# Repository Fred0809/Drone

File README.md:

# Drone

This is a one shared repository for four separate ones I've been working on previously. It consists of Electronic Soeed Controller (ESC), Flight Controller Unit (FCU), Power Distribution Board (PDB), and Remote Controller (RC) hardware projects. The initial idea was supposed to use these four to make a working flying drone. Currently they only show what I've been doing when I first started PCB journey with some of design choices and my very limited knowledge and skillset back then. And at this time none of them is being worked on anymore.

ESC:

FCU:

PDB:

RC:

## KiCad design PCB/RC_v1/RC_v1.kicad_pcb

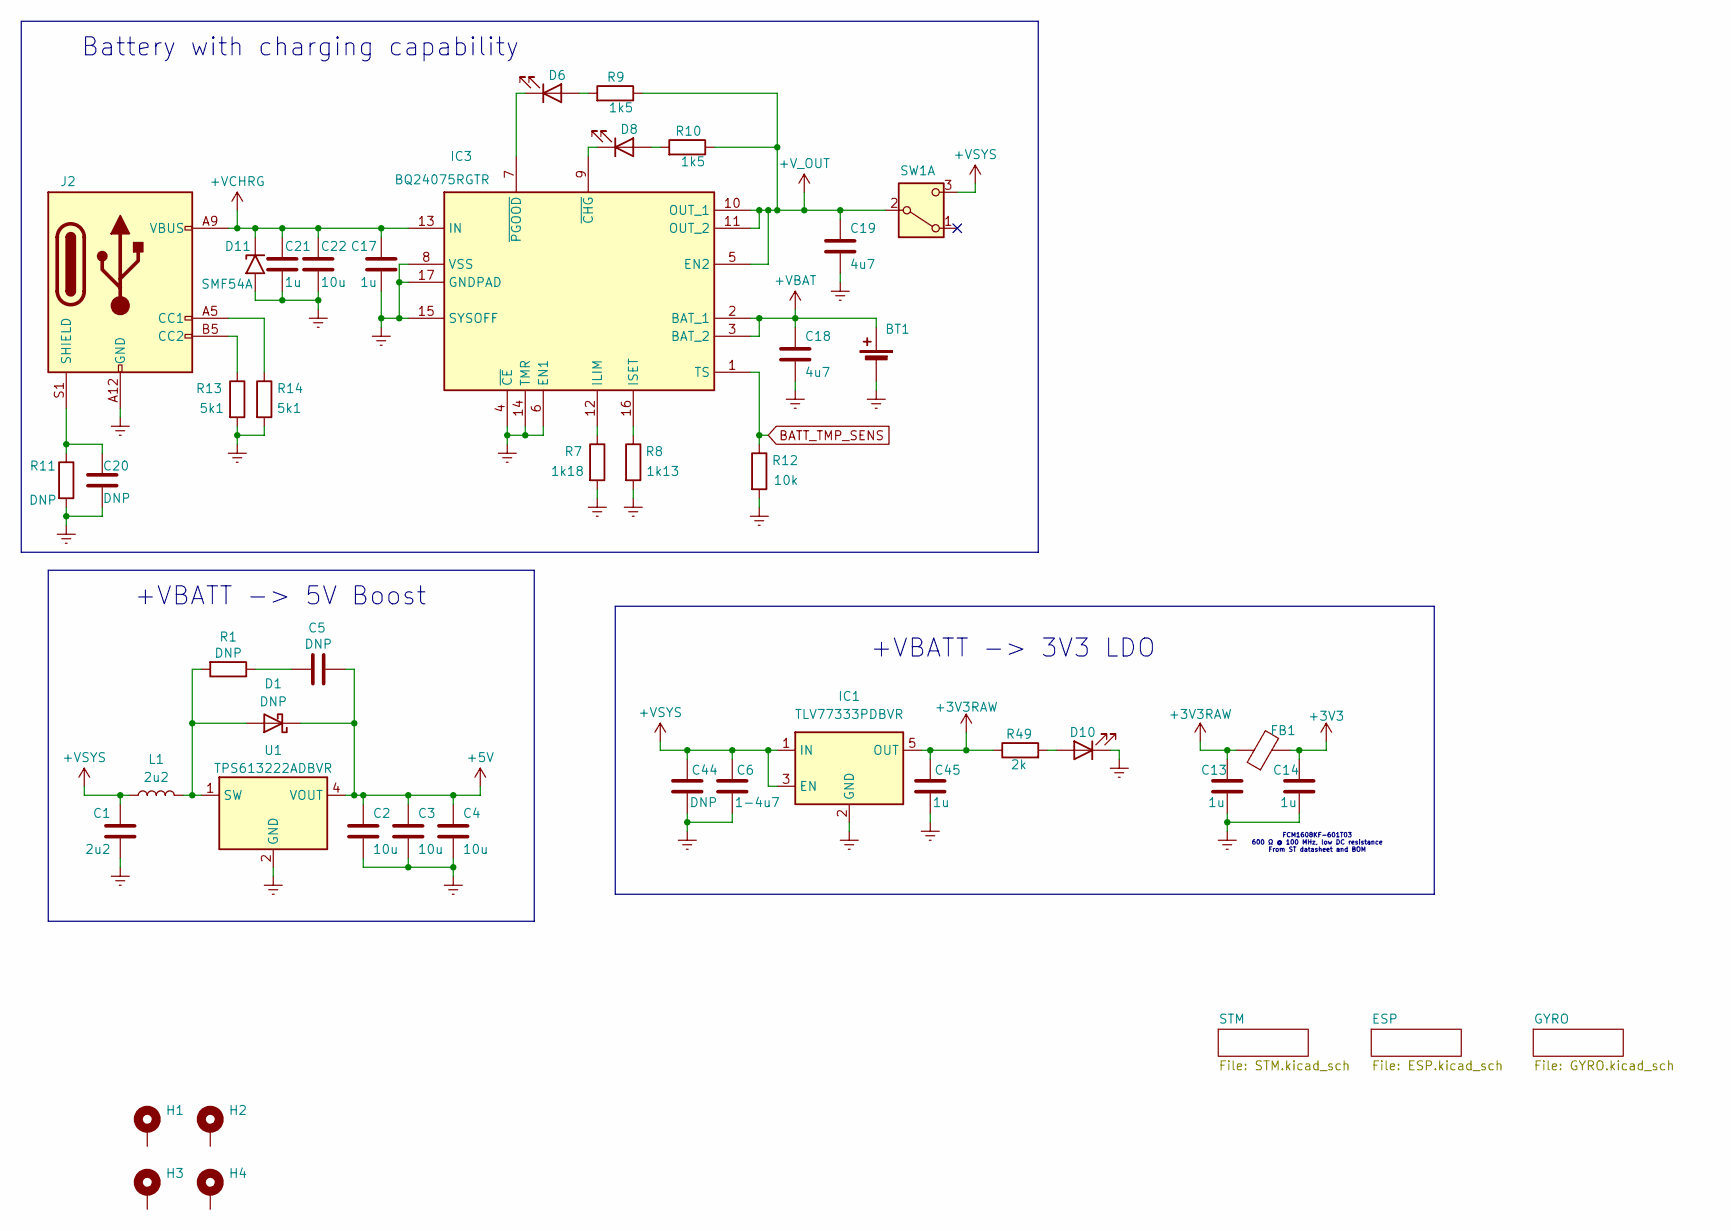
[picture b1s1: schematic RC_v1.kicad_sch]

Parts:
BT1: Battery_Cell
C1: 2u2; C_0603_1608Metric
C2, C3, C4, C22: 10u; C_0603_1608Metric
C5: DNP; C_0805_2012Metric
C6: 1-4u7; C_0603_1608Metric
C13, C14, C45: 1u; C_0603_1608Metric
C17, C21: 1u; C_0402_1005Metric
C18, C19: 4u7; C_0603_1608Metric
C20, C44: DNP; C_0603_1608Metric
D1: DNP; D_0603_1608Metric
D6, D8, D10: LED; LED_0805_2012Metric
D11: SMF54A; D_SMF
FB1: FCM1608KF-601T03; L_0603_1608Metric
H1, H2, H3, H4: MountingHole_Pad; MountingHole_2.2mm_M2_Pad
IC1: TLV77333PDBVR; SOT95P280X145-5N; Mouser Part Number 595-TLV77333PDBVR
IC3: BQ24075RGTR; QFN50P300X300X100-17N-D; Mouser Part Number 595-BQ24075RGTR
J2: USB_C_Receptacle_PowerOnly_6P; USB_C_Receptacle_GCT_USB4125-xx-x_6P_TopMnt_Horizontal
L1: 2u2; WE-MAPI_4020; Mouser Part Number 710-74438356022
R1, R11: DNP; R_0603_1608Metric
R7: 1k18; R_0603_1608Metric
R8: 1k13; R_0603_1608Metric
R9, R10: 1k5; R_0603_1608Metric
R12: 10k; R_0603_1608Metric
R13, R14: 5k1; R_0603_1608Metric
R49: 2k; R_0603_1608Metric
SW1: SW_DPDT_x2; SW_CK_JS202011AQN_DPDT_Angled
U1: TPS613222ADBVR; SOT-23-5

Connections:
+3V3: C14.1, FB1.2; also elsewhere on the board
+3V3RAW: C13.1, C45.1, FB1.1, IC1.5 (OUT), R49.1
+5V: C2.1, C3.1, C4.1, C5.2, D1.1 (K), U1.4 (VOUT); also elsewhere on the board
+VBAT: BT1.1 (+), C18.1, IC3.2 (BAT_1), IC3.3 (BAT_2)
+VCHRG: C17.1, C21.1, C22.1, D11.1 (A1), IC3.13 (IN), J2.A9 (VBUS), J2.B9 (VBUS)
+VSYS: C1.1, C6.1, C44.1, IC1.1 (IN), IC1.3 (EN), L1.1, SW1.3 (C)
+V_OUT: C19.1, IC3.5 (EN2), IC3.10 (OUT_1), IC3.11 (OUT_2), R9.1, R10.1, SW1.2 (B)
BATT_TMP_SENS: IC3.1 (TS), R12.1
GND: BT1.2 (-), C1.2, C2.2, C3.2, C4.2, C6.2, C13.2, C14.2, C17.2, C18.2, C19.2, C20.2, C21.2, C22.2, C44.2, C45.2, D10.1 (K), D11.2 (A2), IC1.2 (GND), IC3.4 (~CE), IC3.6 (EN1), IC3.8 (VSS), IC3.14 (TMR), IC3.15 (SYSOFF), IC3.17 (GNDPAD), J2.A12 (GND), J2.B12 (GND), R7.2, R8.2, R11.2, R12.2, R13.2, R14.2, U1.2 (GND); also elsewhere on the board
unnamed: C5.1, R1.1
unnamed: D1.2 (A), L1.2, R1.2, U1.1 (SW)
unnamed: D6.2 (A), R9.2
unnamed: D6.1 (K), IC3.7 (~PGOOD)
unnamed: D8.2 (A), R10.2
unnamed: D8.1 (K), IC3.9 (~CHG)
unnamed: D10.2 (A), R49.2
unnamed: IC3.12 (ILIM), R7.1
unnamed: IC3.16 (ISET), R8.1
unnamed: J2.A5 (CC1), R14.1
unnamed: J2.B5 (CC2), R13.1
unnamed: C20.1, J2.S1 (SHIELD), R11.1

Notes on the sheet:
FCM1608KF-601T03 600 Ω @ 100 MHz, low DC resistance From ST datasheet and BOM
+VBATT -> 3V3 LDO
Battery with charging capability
+VBATT -> 5V Boost

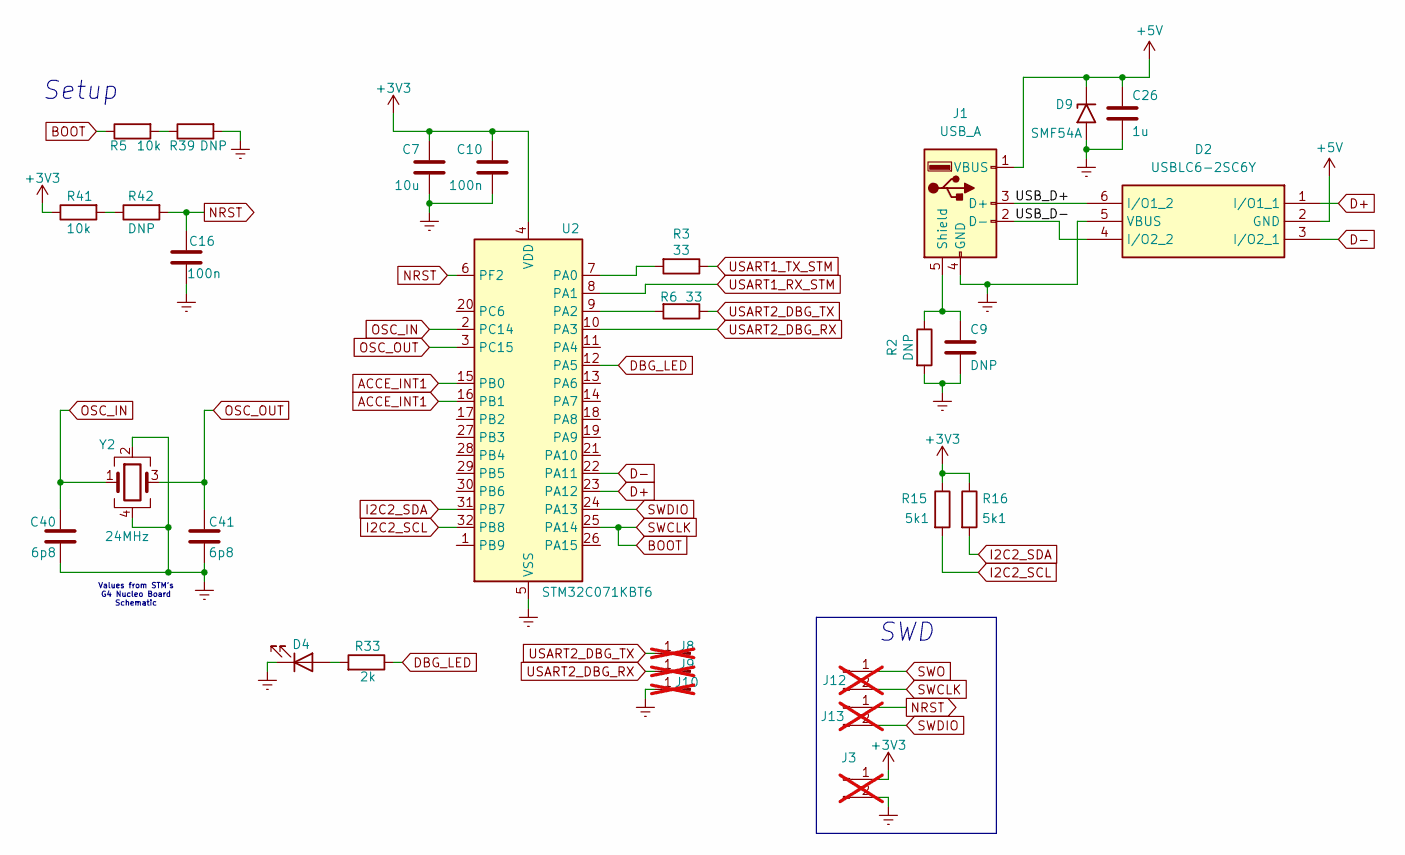
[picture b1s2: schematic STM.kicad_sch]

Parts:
C7: 10u; C_0603_1608Metric
C9: DNP; C_0603_1608Metric
C10, C16: 100n; C_0402_1005Metric
C26: 1u; C_0603_1608Metric
C40, C41: 6p8; C_0402_1005Metric
D2: USBLC6-2SC6Y; SOT95P280X145-6N; Mouser Part Number 511-USBLC6-2SC6Y
D4: LED; LED_0805_2012Metric
D9: SMF54A; D_SMF
J1: USB_A; USB_A_Molex_67643_Horizontal
J3, J12, J13: Conn_01x02_Pin; PinHeader_1x02_P2.54mm_Vertical; not fitted
J8, J9, J10: Conn_01x01_Pin; PinHeader_1x01_P2.54mm_Vertical; not fitted
R2: DNP; R_0603_1608Metric
R3, R6: 33; R_0603_1608Metric
R5, R41: 10k; R_0603_1608Metric
R15, R16: 5k1; R_0603_1608Metric
R33: 2k; R_0603_1608Metric
R39, R42: DNP; R_0402_1005Metric
U2: STM32C071KBT6; LQFP-32_7x7mm_P0.8mm
Y2: 24MHz; Crystal_SMD_3225-4Pin_3.2x2.5mm

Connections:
+3V3: C7.1, C10.1, J3.1, R15.1, R16.1, R41.1, U2.4 (VDD); also elsewhere on the board
+5V: C26.1, D2.2 (GND), D9.1 (A1), J1.1 (VBUS); also elsewhere on the board
/STM/USB_D+: D2.6 (I/O1_2), J1.3 (D+)
/STM/USB_D-: D2.4 (I/O2_2), J1.2 (D-)
ACCE_INT1: U2.15 (PB0), U2.16 (PB1); also elsewhere on the board
BOOT: J12.2, R5.1, U2.25 (PA14)
D+: D2.1 (I/O1_1), U2.23 (PA12)
D-: D2.3 (I/O2_1), U2.22 (PA11)
DBG_LED: R33.1, U2.12 (PA5)
GND: C7.2, C9.2, C10.2, C16.2, C26.2, C40.2, C41.2, D2.5 (VBUS), D4.1 (K), D9.2 (A2), J1.4 (GND), J3.2, J10.1 (Pin_1_1), R2.2, R39.2, U2.5 (VSS), Y2.2, Y2.4; also elsewhere on the board
I2C2_SCL: R15.2, U2.32 (PB8); also elsewhere on the board
I2C2_SDA: R16.2, U2.31 (PB7); also elsewhere on the board
NRST: C16.1, J13.1, R42.2, U2.6 (PF2)
unnamed: D4.2 (A), R33.2
unnamed: C9.1, J1.5 (Shield), R2.1
unnamed: R5.2, R39.1
unnamed: R41.2, R42.1
unnamed: R3.2, U2.7 (PA0)
unnamed: R6.2, U2.9 (PA2)
OSC_IN: C40.1, U2.2 (PC14), Y2.1
OSC_OUT: C41.1, U2.3 (PC15), Y2.3
SWDIO: J13.2, U2.24 (PA13)
SWO: J12.1
USART1_RX_STM: U2.8 (PA1); also elsewhere on the board
USART1_TX_STM: R3.1; also elsewhere on the board
USART2_DBG_RX: J9.1 (Pin_1_1), U2.10 (PA3)
USART2_DBG_TX: J8.1 (Pin_1_1), R6.1

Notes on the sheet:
Setup
Values from STM's G4 Nucleo Board Schematic
SWD

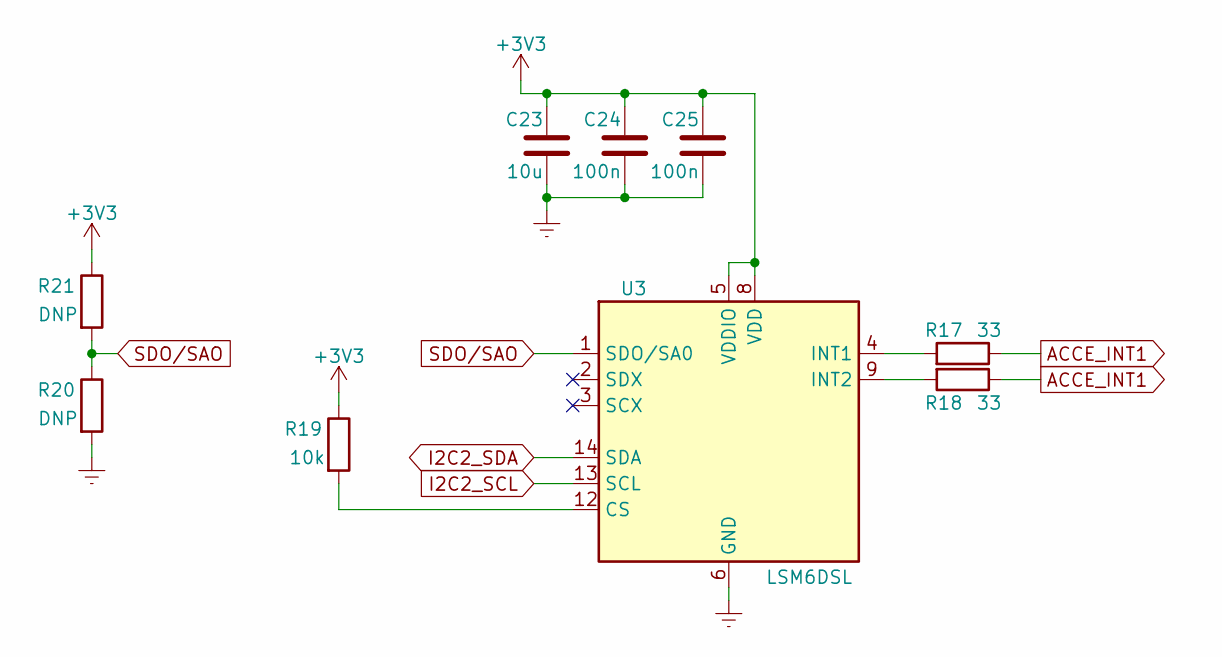
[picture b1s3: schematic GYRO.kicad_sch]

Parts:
C23: 10u; C_0603_1608Metric
C24, C25: 100n; C_0402_1005Metric
R17, R18: 33; R_0603_1608Metric
R19: 10k; R_0603_1608Metric
R20, R21: DNP; R_0402_1005Metric
U3: LSM6DSL; LGA-14_3x2.5mm_P0.5mm_LayoutBorder3x4y

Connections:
+3V3: C23.1, C24.1, C25.1, R19.1, R21.1, U3.5 (VDDIO), U3.8 (VDD); also elsewhere on the board
ACCE_INT1: R17.1, R18.1; also elsewhere on the board
GND: C23.2, C24.2, C25.2, R20.2, U3.6 (GND), U3.7 (GND); also elsewhere on the board
I2C2_SCL: U3.13 (SCL); also elsewhere on the board
I2C2_SDA: U3.14 (SDA); also elsewhere on the board
unnamed: R19.2, U3.12 (CS)
unnamed: R17.2, U3.4 (INT1)
unnamed: R18.2, U3.9 (INT2)
SDO/SAO: R20.1, R21.2, U3.1 (SDO/SA0)

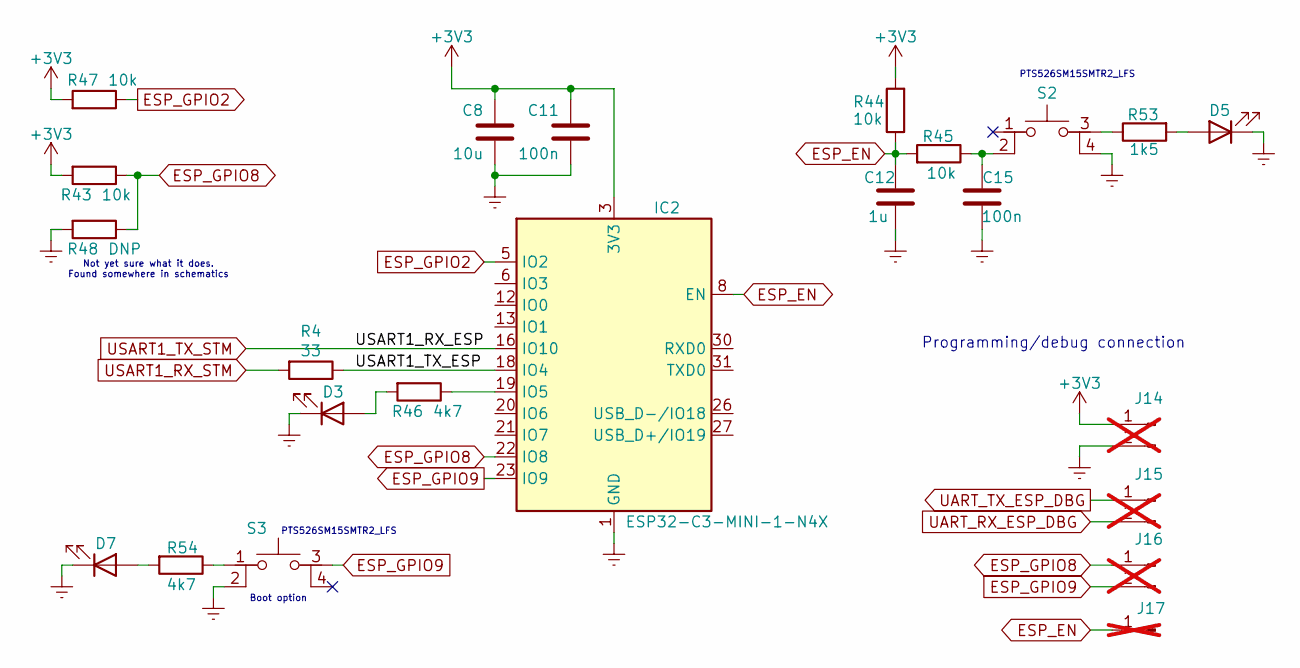
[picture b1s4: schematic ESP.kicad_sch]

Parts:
C8: 10u; C_0603_1608Metric
C11: 100n; C_0402_1005Metric
C12: 1u; C_0402_1005Metric
C15: 100n; C_0805_2012Metric
D3, D5, D7: LED; LED_0805_2012Metric
IC2: ESP32-C3-MINI-1-N4X; ESP32C3MINI1N4X; Manufacturer_Part_Number ESP32-C3-MINI-1-N4X
J14, J15, J16: Conn_01x02_Pin; PinHeader_1x02_P2.54mm_Vertical; not fitted
J17: Conn_01x01_Pin; PinHeader_1x01_P2.54mm_Vertical; not fitted
R4: 33; R_0603_1608Metric
R43, R44, R45, R47: 10k; R_0603_1608Metric
R46, R54: 4k7; R_0603_1608Metric
R48: DNP; R_0402_1005Metric
R53: 1k5; R_0603_1608Metric
S2, S3: PTS526SM15SMTR2_LFS; PTS526SM15SMTR2LFS; Mouser Part Number 611-PTS526SM15SMTR2L

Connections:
+3V3: C8.1, C11.1, IC2.3 (3V3), J14.1, R43.2, R44.2, R47.2; also elsewhere on the board
/ESP/USART1_TX_ESP: IC2.18 (IO4), R4.1
ESP_EN: C12.1, IC2.8 (EN), J17.1 (Pin_1_1), R44.1, R45.2
ESP_GPIO2: IC2.5 (IO2), R47.1
ESP_GPIO8: IC2.22 (IO8), J16.1, R43.1, R48.1
ESP_GPIO9: IC2.23 (IO9), J16.2, S3.3 (NO_1)
GND: C8.2, C11.2, C12.2, C15.2, D3.1 (K), D5.1 (K), D7.1 (K), IC2.1 (GND), IC2.2 (GND_2), IC2.11 (GND_3), IC2.14 (GND_4), IC2.36 (GND_5), IC2.37 (GND_6), IC2.38 (GND_7), IC2.39 (GND_8), IC2.40 (GND_9), IC2.41 (GND_10), IC2.42 (GND_11), IC2.43 (GND_12), IC2.44 (GND_13), IC2.45 (GND_14), IC2.46 (GND_15), IC2.47 (GND_16), IC2.48 (GND_17), IC2.49 (GND_18), IC2.50 (GND_19), IC2.51 (GND_20), IC2.52 (GND_21), IC2.53 (GND_22), IC2.54 (GND_23), IC2.55 (GND_24), IC2.56 (GND_25), IC2.57 (GND_26), IC2.58 (GND_27), IC2.59 (GND_28), IC2.60 (GND_29), IC2.61 (GND_30), J14.2, R48.2, S2.4 (NO_2), S3.2 (COM_2); also elsewhere on the board
unnamed: D3.2 (A), R46.2
unnamed: D5.2 (A), R53.2
unnamed: D7.2 (A), R54.2
unnamed: IC2.19 (IO5), R46.1
unnamed: C15.1, R45.1, S2.2 (COM_2)
unnamed: R53.1, S2.3 (NO_1)
unnamed: R54.1, S3.1 (COM_1)
UART_RX_ESP_DBG: J15.2
UART_TX_ESP_DBG: J15.1
USART1_RX_STM: R4.2; also elsewhere on the board
USART1_TX_STM: IC2.16 (IO10); also elsewhere on the board

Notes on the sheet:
Programming/debug connection
PTS526SM15SMTR2_LFS
Not yet sure what it does. Found somewhere in schematics
Boot option

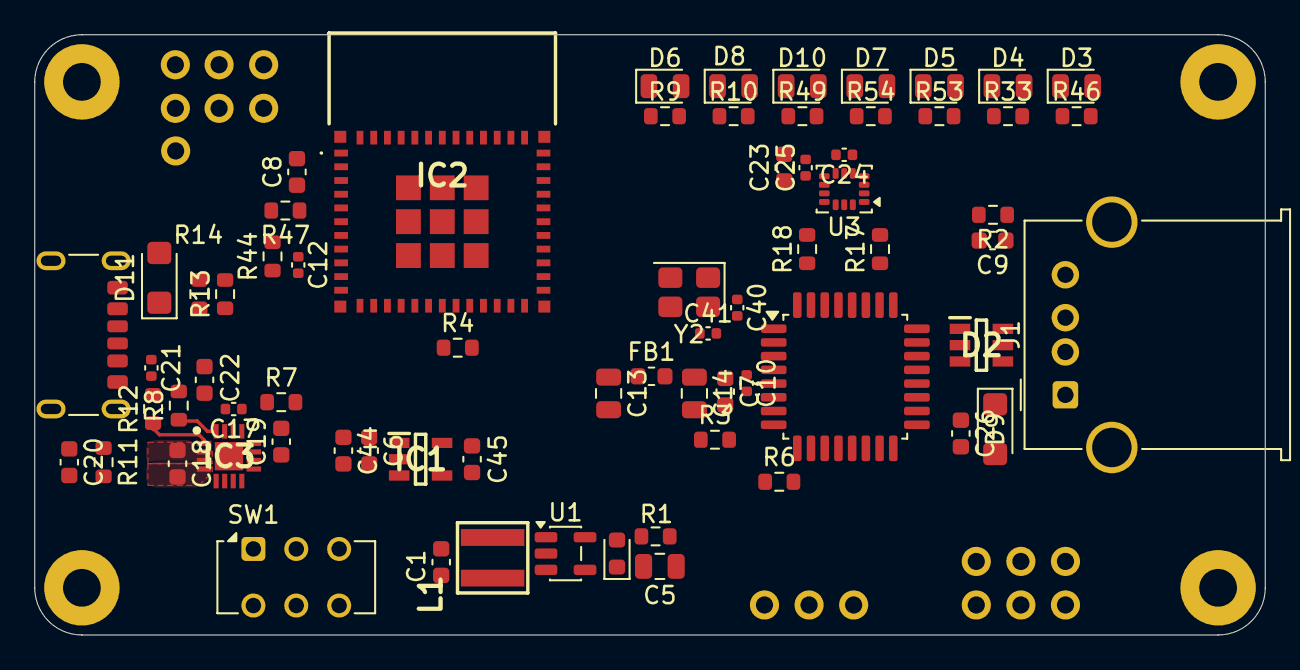
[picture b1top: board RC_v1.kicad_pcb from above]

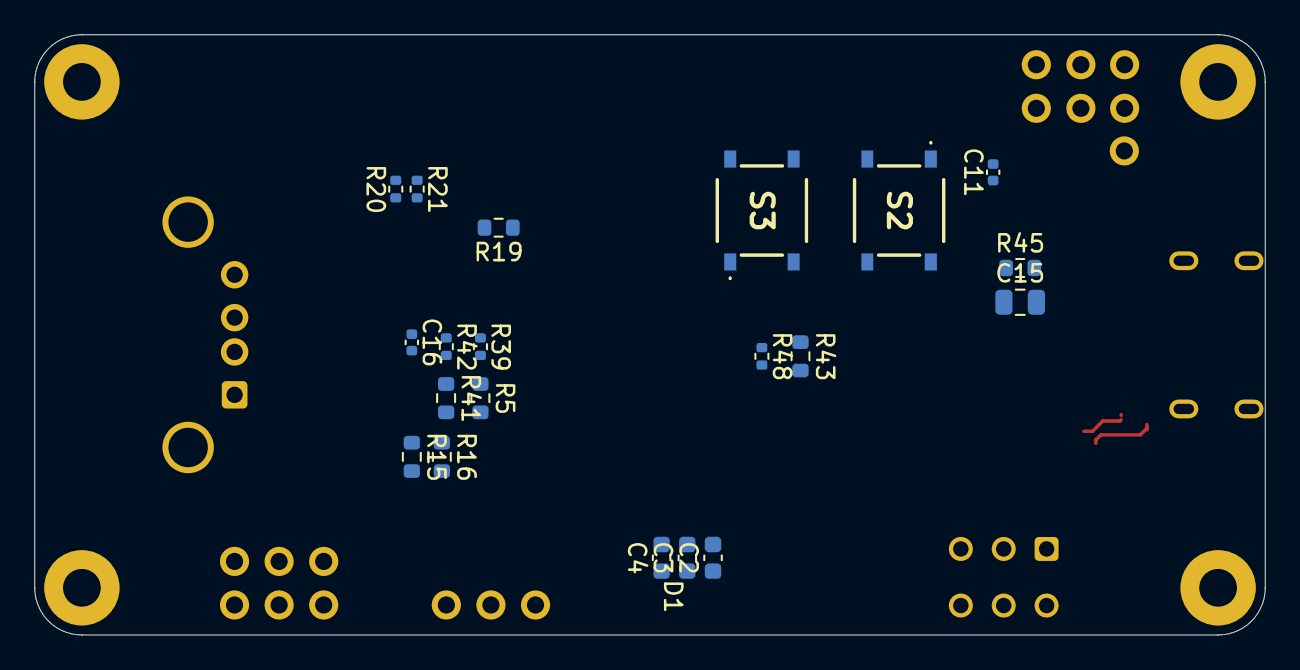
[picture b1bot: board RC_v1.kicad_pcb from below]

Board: 4 copper layers, 71.8 x 35.0 mm, 103 parts (20 on the bottom side), 60 nets.

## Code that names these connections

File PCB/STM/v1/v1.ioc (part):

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Mcu.Name=STM32C071KBTx
Mcu.Package=LQFP32_GP
Mcu.UserName=STM32C071KBTx
PA0.Mode=Asynchronous
PA0.Signal=USART1_TX
PA1.Mode=Asynchronous
PA1.Signal=USART1_RX
PA11\ [PA9].Mode=Host
PA11\ [PA9].Signal=USB_DM
PA12\ [PA10].Mode=Host
PA12\ [PA10].Signal=USB_DP
PA13.Mode=Serial_Wire
PA13.Signal=DEBUG_SWDIO
PA14-BOOT0.Mode=Serial_Wire
PA14-BOOT0.Signal=DEBUG_SWCLK
PA2.Mode=Asynchronous
PA2.Signal=USART2_TX
PA3.Mode=Asynchronous
PA3.Signal=USART2_RX
PA5.GPIOParameters=GPIO_Label
PA5.GPIO_Label=DBG_LED
PA5.Signal=GPIO_Output
PB0.GPIOParameters=GPIO_Label
PB0.GPIO_Label=INT1
PB0.Signal=GPIO_Input
PB1.GPIOParameters=GPIO_Label
PB1.GPIO_Label=INT2
PB1.Signal=GPIO_Input
PB7.Mode=I2C
PB7.Signal=I2C1_SDA
PB8.Mode=I2C
PB8.Signal=I2C1_SCL
PC14-OSCX_IN(PC14).Mode=HSE-External-Oscillator
PC14-OSCX_IN(PC14).Signal=RCC_OSCX_IN
PC15-OSCX_OUT(PC15).Mode=HSE-External-Oscillator
PC15-OSCX_OUT(PC15).Signal=RCC_OSCX_OUT
PF2-NRST.GPIOParameters=GPIO_Label
PF2-NRST.GPIO_Label=NRST
PF2-NRST.Signal=GPIO_Input
RCC.HSE_VALUE=8000000
RCC.SYSCLKFreq_VALUE=12000000
board=custom

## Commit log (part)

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2026-03-18 Schematic and layout update
2026-05-10 Layout updated
